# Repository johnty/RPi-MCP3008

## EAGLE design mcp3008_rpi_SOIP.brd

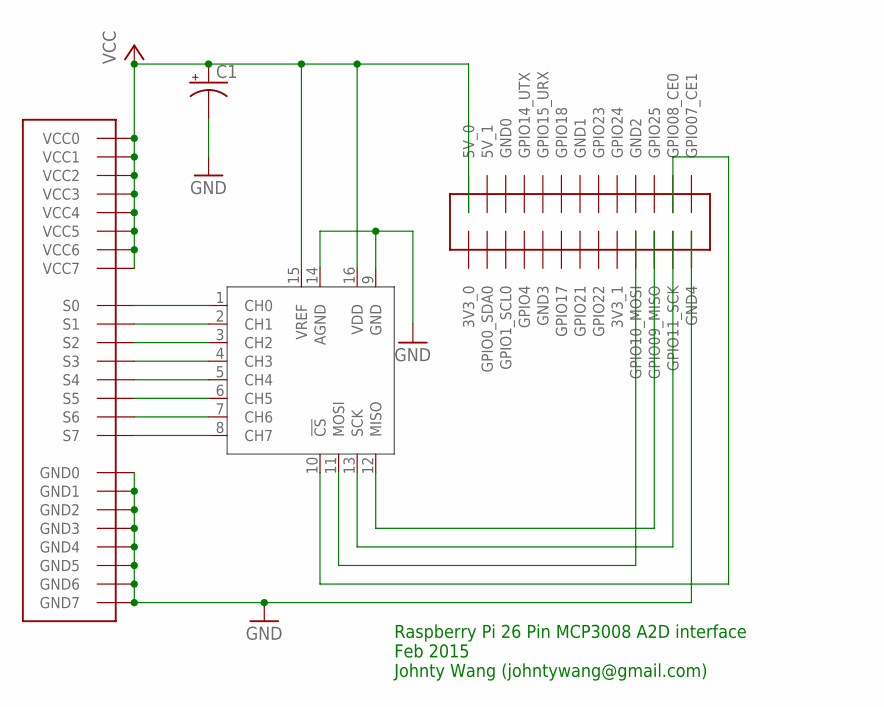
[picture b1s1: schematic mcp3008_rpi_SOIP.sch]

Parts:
C1: CPOL-USE2.5-6; E2,5-6
U$1: 3BY83X8_SAMTEC; 3X8_PKG
U$2: RPI_26; RPI26
U$3: MCP3008SL; SO16

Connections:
GND: C1.-, U$1.GND0, U$1.GND1, U$1.GND2, U$1.GND3, U$1.GND4, U$1.GND5, U$1.GND6, U$1.GND7, U$2.GND4, U$3.9 (GND), U$3.14 (AGND)
unnamed: U$1.S0, U$3.1 (CH0)
unnamed: U$1.S1, U$3.2 (CH1)
unnamed: U$1.S2, U$3.3 (CH2)
unnamed: U$1.S3, U$3.4 (CH3)
unnamed: U$1.S4, U$3.5 (CH4)
unnamed: U$1.S5, U$3.6 (CH5)
unnamed: U$1.S6, U$3.7 (CH6)
unnamed: U$1.S7, U$3.8 (CH7)
unnamed: U$2.GPIO09 (GPIO09_MISO), U$3.12 (MISO)
unnamed: U$2.GPIO11 (GPIO11_SCK), U$3.13 (SCK)
unnamed: U$2.GPIO10 (GPIO10_MOSI), U$3.11 (MOSI)
unnamed: U$2.GPIO08 (GPIO08_CE0), U$3.10 (!CS)
VCC: C1.+, U$1.VCC0, U$1.VCC1, U$1.VCC2, U$1.VCC3, U$1.VCC4, U$1.VCC5, U$1.VCC6, U$1.VCC7, U$2.5V0 (5V_0), U$3.15 (VREF), U$3.16 (VDD)

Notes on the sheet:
Raspberry Pi 26 Pin MCP3008 A2D interface Feb 2015 Johnty Wang (johntywang@gmail.com)

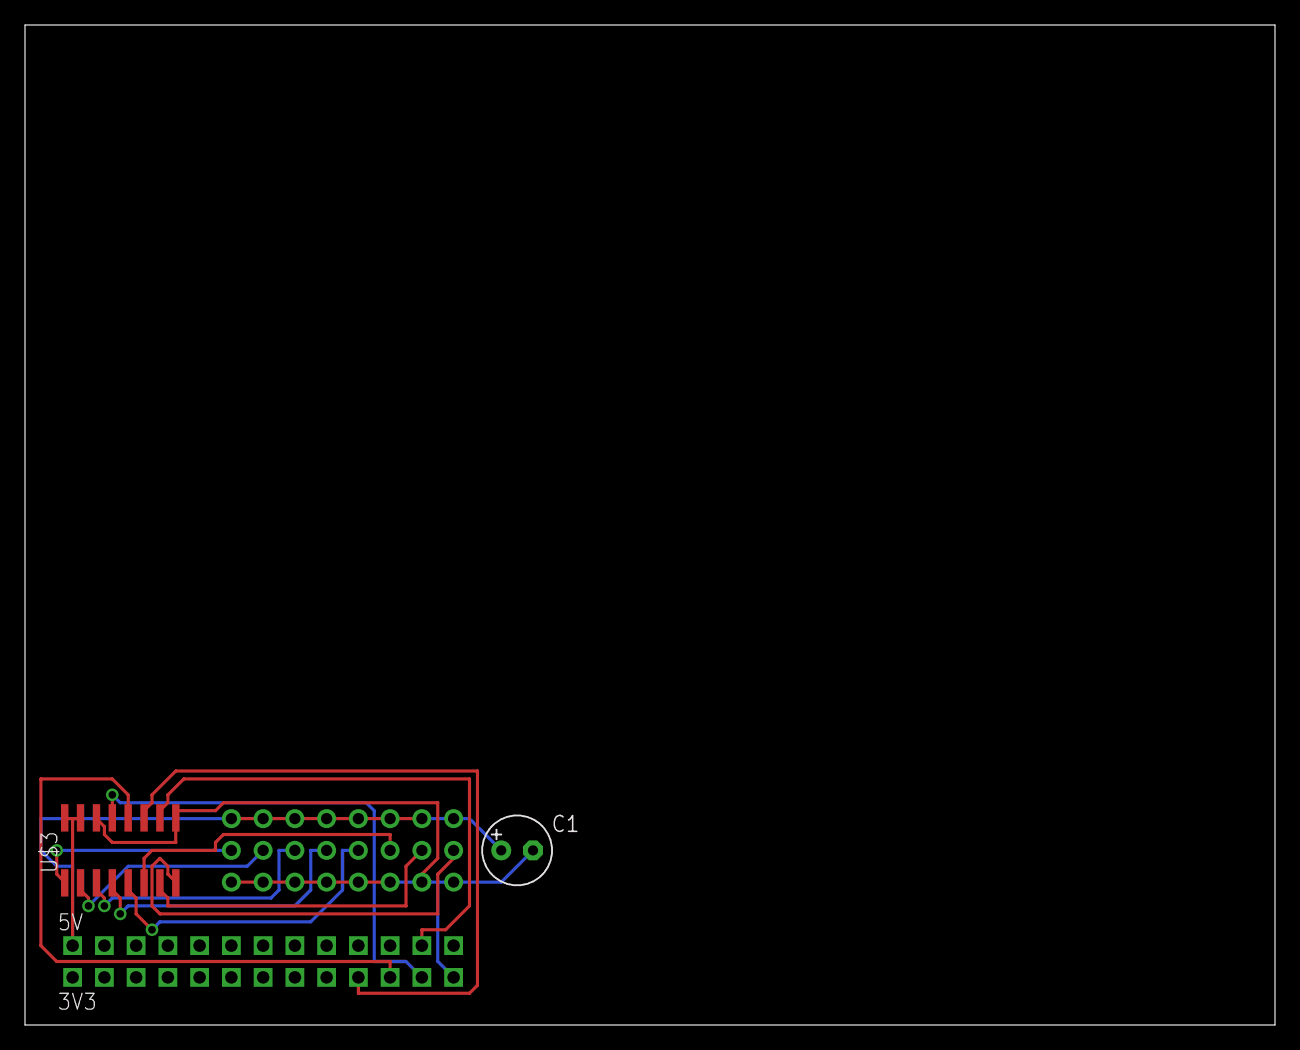
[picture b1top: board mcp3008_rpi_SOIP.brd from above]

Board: 2 copper layers, 100.0 x 80.0 mm, 4 parts (0 on the bottom side), 14 nets.

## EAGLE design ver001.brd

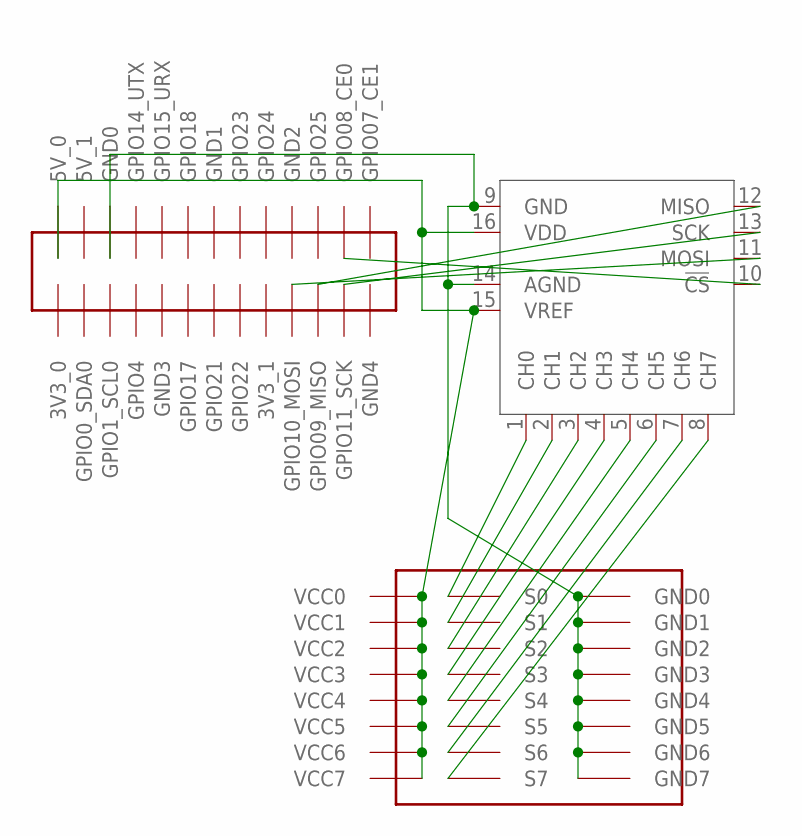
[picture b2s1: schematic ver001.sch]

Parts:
U$1: RPI_26; RPI26
U$2: MCP3008P; DIL16
U$3: 3BY8; 3BY8HEADER

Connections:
unnamed: U$2.1 (CH0), U$3.S0
unnamed: U$2.2 (CH1), U$3.S1
unnamed: U$2.3 (CH2), U$3.S2
unnamed: U$2.4 (CH3), U$3.S3
unnamed: U$2.5 (CH4), U$3.S4
unnamed: U$1.GPIO11 (GPIO11_SCK), U$2.13 (SCK)
unnamed: U$1.GPIO09 (GPIO09_MISO), U$2.12 (MISO)
unnamed: U$2.6 (CH5), U$3.S5
unnamed: U$1.GPIO10 (GPIO10_MOSI), U$2.11 (MOSI)
unnamed: U$2.7 (CH6), U$3.S6
unnamed: U$2.8 (CH7), U$3.S7
unnamed: U$1.5V0 (5V_0), U$2.15 (VREF), U$2.16 (VDD), U$3.VCC0, U$3.VCC1, U$3.VCC2, U$3.VCC3, U$3.VCC4, U$3.VCC5, U$3.VCC6, U$3.VCC7
unnamed: U$1.GND0, U$2.9 (GND), U$2.14 (AGND), U$3.GND0, U$3.GND1, U$3.GND2, U$3.GND3, U$3.GND4, U$3.GND5, U$3.GND6, U$3.GND7

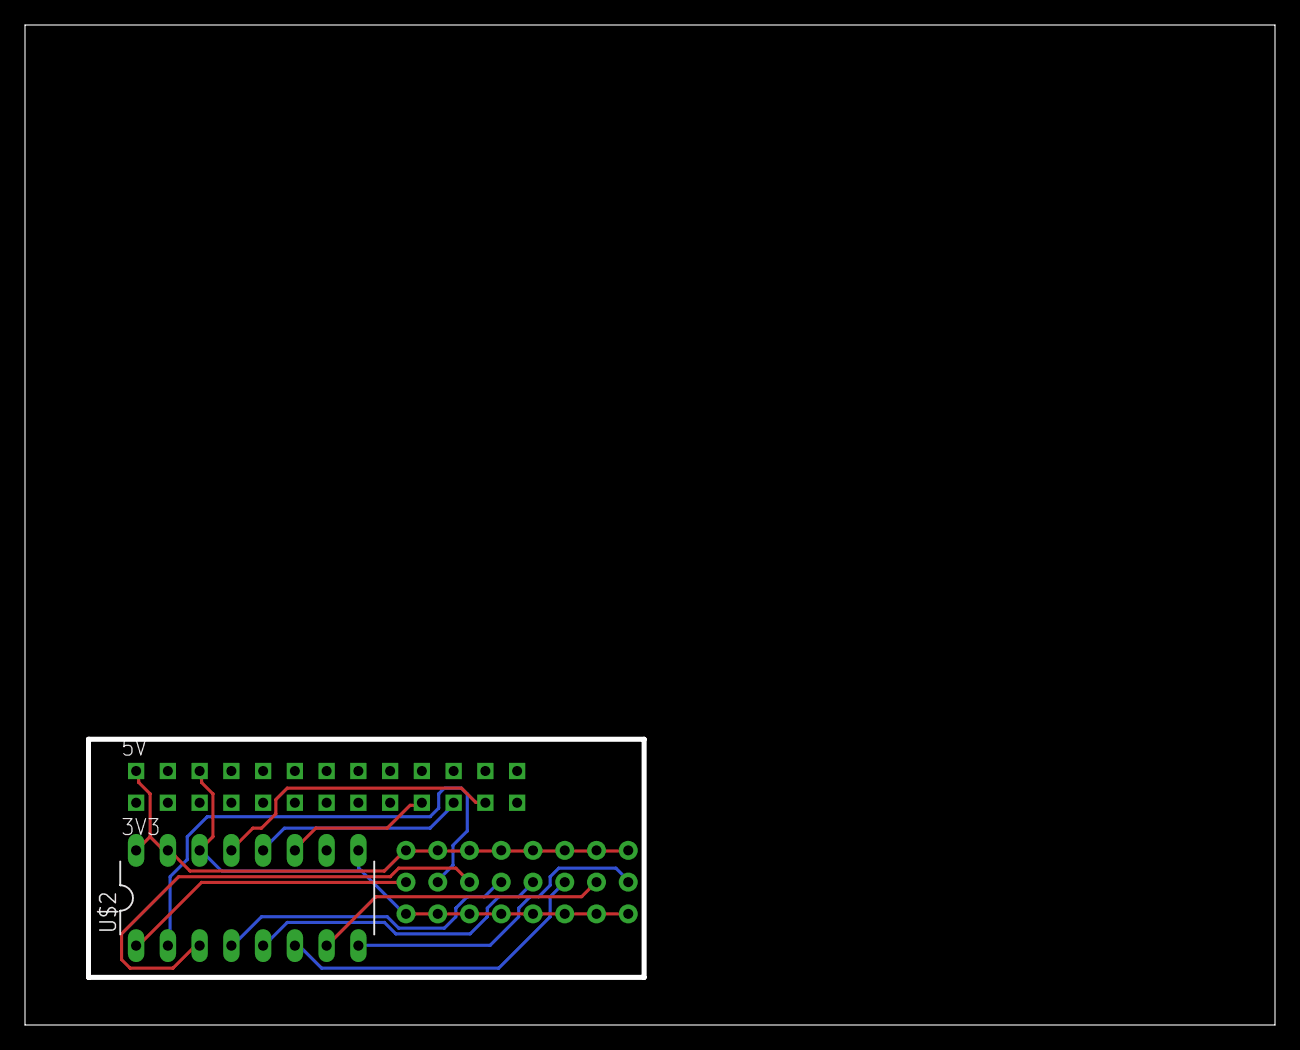
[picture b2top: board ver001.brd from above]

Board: 2 copper layers, 100.0 x 80.0 mm, 3 parts (0 on the bottom side), 13 nets.

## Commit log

2015-04-23 final version before manufacture
2015-07-09 updated library with i2c header package, and main board with i2c
2015-07-09 i2c board complete
